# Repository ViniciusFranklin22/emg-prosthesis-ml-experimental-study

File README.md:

# Undergraduate Thesis – EMG Signal Analysis and Classification of Forearm Muscles

This repository contains all files related to the Undergraduate Thesis (**Trabalho de Conclusão de Curso – TCC**) developed by **Vinícius Franklin**, as part of the Electrical Engineering – Electronic Systems undergraduate program.

The work focuses on the acquisition, processing, feature extraction, and classification of electromyographic (EMG) signals collected from different forearm muscles. Distinct movement patterns are analyzed, and both unsupervised and supervised machine learning techniques are applied to evaluate signal individuality and classification performance.

---

## 📄 Thesis Documents

* **Thesis (Portuguese):** [TCC_Vinicius_Franklin.pdf](./TCC_Vinicius_Franklin.pdf)
* **Thesis (English):** [TCC_Vinicius_Franklin_eng.pdf](./TCC_Vinicius_Franklin_eng.pdf)

These documents describe the experimental setup, signal acquisition methodology, preprocessing stages, feature extraction methods, and the development and evaluation of classification models.

---

## 📂 Repository Organization

The repository is structured according to the organization of the thesis and the experimental configurations adopted during EMG signal acquisition.

## 🔧 Hardware Design – EMG Sensor (KiCad)

This repository includes the **dedicated PCB design** of the EMG sensor used in the experimental setup.  
The hardware was designed using **KiCad**, including schematic capture, PCB layout, and project configuration files.

### 📁 KiCad
The following KiCad files are versioned to ensure full reproducibility of the hardware design:

- `.kicad_pro` → KiCad project file  
- `.kicad_sch` → Schematic design  
- `.kicad_pcb` → PCB layout and routing  

### 🔹 Acquisition Configurations
Each configuration corresponds to a specific forearm muscle:

1.  **First Configuration** → Flexor Carpi Radialis
2.  **Second Configuration** → Flexor Pollicis Longus
3.  **Third Configuration** → Flexor Digitorum Superficialis
4.  **Fourth Configuration** → Extensor Digitorum

Each configuration folder contains the raw datasets, extracted features, and machine learning models related to the respective muscle.

### 📊 EMG Signal Datasets
Within each configuration folder, approximately five `.csv` files are provided, corresponding to the following movement patterns:

* Relaxed muscle
* Contracted muscle
* Contraction and relaxation movement (~10-second period)
* Contraction and relaxation movement (~5-second period)
* Contraction and relaxation of each individual finger (~5-second period), aiming to analyze signal interference and the individuality of muscle activation.

---

## 🧠 Feature Extraction and Model Structure

To ensure clarity and reproducibility, the internal structure of each configuration follows this pattern:

```text
Number Configuration/
│
├── Models/
│   ├── Unsupervised/
│   └── Supervised/
│
└── Features Dataset/
```

### 🔹 Models/Unsupervised
Contains Jupyter notebooks (`.ipynb`) for feature extraction and unsupervised classification. Execution generates a `.csv` file with extracted features and labels. Each notebook documents how optimal parameters were obtained.

### 🔹 Models/Supervised
Contains notebooks that merge the labeled feature datasets within the same configuration to train and evaluate the supervised classification models.

### 🔹 Features Dataset
Contains all feature datasets generated by the unsupervised models, properly formatted for direct use in supervised learning.

---

## ▶️ Code Execution Guidelines
The codes were developed primarily using **Google Colab**, but can be executed locally.

### 🔧 Path Configuration (Required)
> [!IMPORTANT]
> Every script and notebook contains a variable named `path = `. You must update this variable to match your local directory structure before execution. This is required for every file.

### 🔧 Google Colab–Specific Code
When running locally, remove or comment out the following line:

```python
drive.mount('/content/drive')
```

## 📦 Dependencies
Install the required Python libraries using:

```bash
pip install -r requirements.txt
```  

## ℹ️ Final Remarks
Since all feature datasets are already generated, you may skip the unsupervised stage and directly execute the supervised models if desired.

## 👤 Author
Vinícius Franklin Undergraduate Student – Electrical Engineering (Electronic Systems)

Federal University of Juiz de Fora (UFJF), Brazil

## 📜 License
This project is intended for academic and research purposes.

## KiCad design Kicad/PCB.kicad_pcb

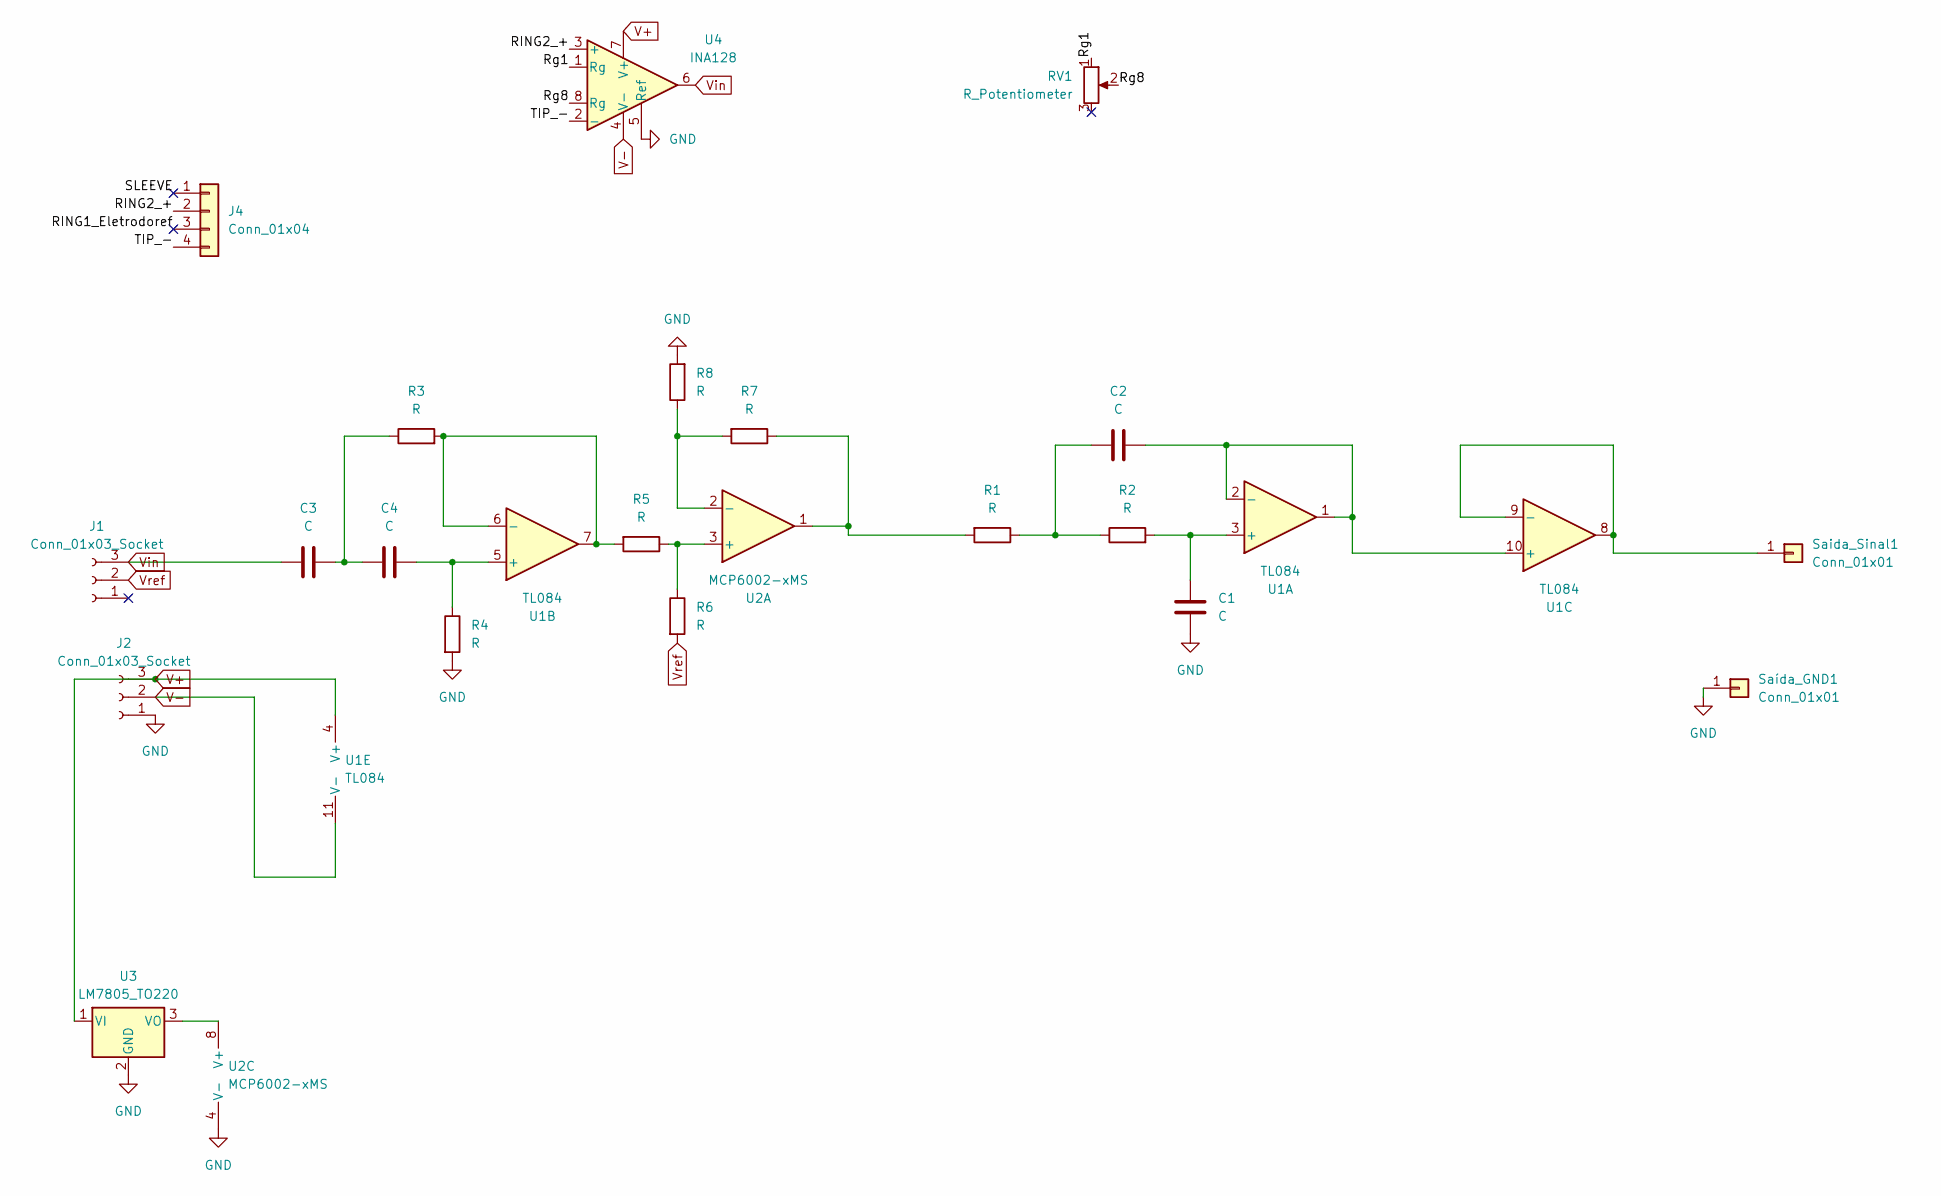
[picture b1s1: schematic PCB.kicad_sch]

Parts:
C1, C2, C3, C4: C; C_Radial_D6.3mm_H11.0mm_P2.50mm
J1, J2: Conn_01x03_Socket; PinHeader_1x03_P2.54mm_Vertical
J4: Conn_01x04; PinSocket_1x04_P2.54mm_Vertical
R1, R2, R3, R4, R5, R6, R7, R8: R; R_Axial_DIN0204_L3.6mm_D1.6mm_P5.08mm_Horizontal
RV1: R_Potentiometer; Potentiometer_Vishay_T93YA_Vertical
Saida_Sinal1: Conn_01x01; PinHeader_1x01_P2.54mm_Vertical
Saída_GND1: Conn_01x01; PinHeader_1x01_P2.54mm_Vertical
U1: TL084; DIP-14_W7.62mm_Socket
U2: MCP6002-xMS; DIP-8_W7.62mm_Socket
U3: LM7805_TO220; TO-220-3_Vertical
U4: INA128; DIP-8_W7.62mm_Socket

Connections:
/RING1_Eletrodoref: J4.3
/RING2_+: J4.2, U4.3 (+)
/Rg1: RV1.1, U4.1 (Rg)
/Rg8: RV1.2, U4.8 (Rg)
/SLEEVE: J4.1
/TIP_-: J4.4, U4.2 (-)
GND: C1.2, J2.1, R4.2, R8.2, Saída_GND1.1, U2.4 (V-), U3.2 (GND), U4.5 (Ref)
unnamed: C2.1, R1.1, R2.1
unnamed: C3.2, C4.1, R3.1
unnamed: R1.2, R7.1, U2.1
unnamed: Saida_Sinal1.1, U1.8, U1.9 (-)
unnamed: C1.1, R2.2, U1.3 (+)
unnamed: C2.2, U1.1, U1.2 (-), U1.10 (+)
unnamed: C4.2, R4.1, U1.5 (+)
unnamed: R3.2, R5.2, U1.6 (-), U1.7
unnamed: R5.1, R6.1, U2.3 (+)
unnamed: R7.2, R8.1, U2.2 (-)
unnamed: U2.8 (V+), U3.3 (VO)
V+: J2.3, U1.4 (V+), U3.1 (VI), U4.7 (V+)
V-: J2.2, U1.11 (V-), U4.4 (V-)
Vin: C3.1, J1.3, U4.6
Vref: J1.2, R6.2

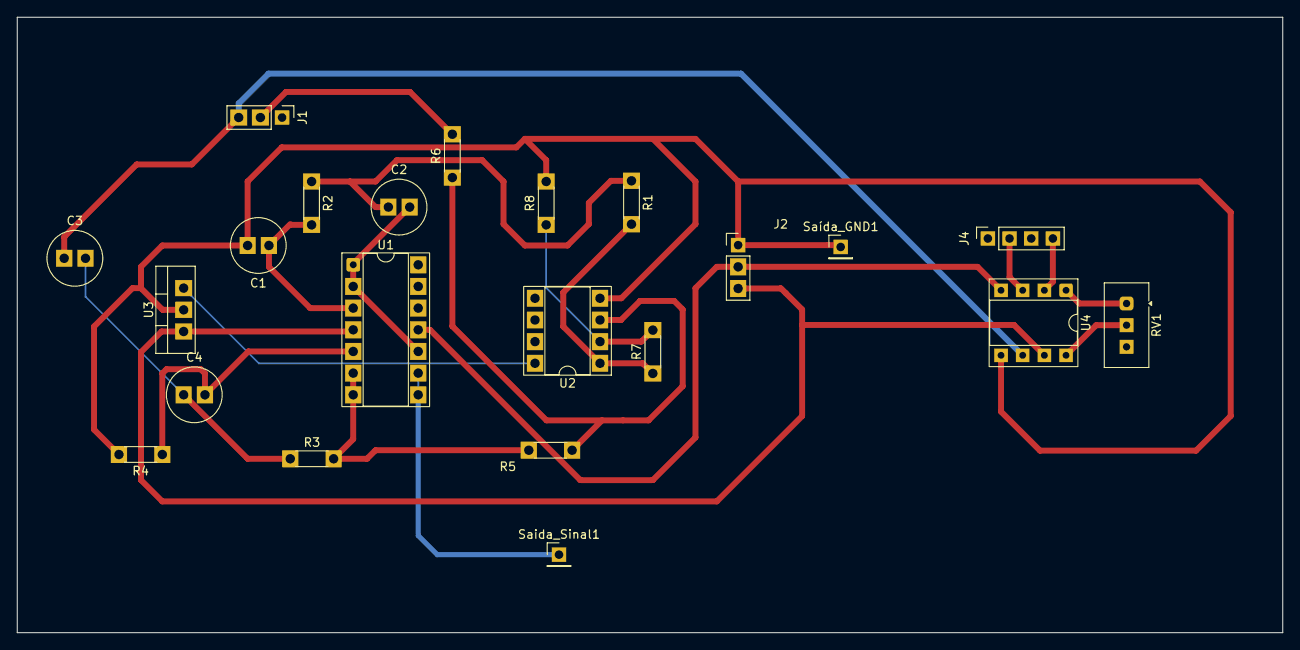
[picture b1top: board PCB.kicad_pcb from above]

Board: 2 copper layers, 148.3 x 72.1 mm, 22 parts (0 on the bottom side), 20 nets.

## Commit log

2026-01-26 Create Second Configuration\
2026-01-26 Create 123
2026-01-26 Create 132
2026-01-28 Create ffff
2026-03-04 Rename TCC_ViniciusFranklin_Corr.pdf to TCC_ViniciusFranklin.pdf
